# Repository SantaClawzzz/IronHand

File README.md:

# Ironhand keyboard

A full-sized keyboard in ZMK. Features a colored TFT screen, encoder, bluetooth connection and a battery.<br>
Numpad is on the left side and switches are easily replaceable with hotswap sockets. Tarkov themed.

* Keyboard specs:
  * 1 nice!nano v2 or nrf52840 pro Micro devkit
  * 1 MCP23S17-E_SO
  * 102 switches (MX)
  * 102 DO-35 diodes (1N4148)
  * 60 100nF 0603 capacitors (Any 100nF)
  * 103 LEDs (WS2812-2020) [One LED under the MCU]
  * One 2000mAh 3.7V LiPo Battery [Bridge the Charging pads under nice!nano]
  * 1 battery connector (JST PH 2.0)
  * 1 0.96" TFT SPI screen
  * 1 encoder
  * 1 button (TL3305A, optional)

## Electronics

The PCB order can be expensive, mostly shipping due to the size. I recommend ordering at least 10 (5 is minimum).<br>
The soldering is mostly fine, hotswap sockets and capacitors are easy but the LEDs are a pain.<br>
My recommendation:
* Solder one corner of the 4 pads on the entire row
* Take a LED and match the polarity
* Solder only by the corner for the entire row
* Then go backwards and solder the same side other corner, turn it and do the other side
  * Easier to do one side at a time
  * Holding the solder iron in the right hand do the right side of the LED
  * Then turn it 180 degrees and solder the other side
  * But to each their own
* the MCP soldering is basically the same, do one corner, align it, then solder the rest of the pins
* Keep in mind that the devkit has a pad under it that needs to be bridged to charge faster if you have a battery bigger than 500mAh!
* Also there is a LED under the devkit on the PCB, solder them first then the devkit on it.
* Otherwise without a desolder gun, you're gonna have a bad time.

## Mechanics

If you wish to change the project files, go ahead. It was designed in Fusion.
Printed with PETG and mostly default settings.
Two halves were attached with a metal plate and staples melted into the PETG halves.

## Firmware

* Connect USB-C
* Open ***Actions*** tab in this github repository
* Download the firmware <br>

* Double press the reset button on the keyboard and drop the file into the file system
  * If you are in bootloader the red LED will constantly blink (nrf pro Micro devkit)

## Notes to consider when building custom keyboard

Read the documentation thoroughly, the directory of the files is VERY IMPORTANT.<br>
It's much more restrict than QMK so it will take some time.<br>
Just try to get it to compile wihtout much code and then start adding features.

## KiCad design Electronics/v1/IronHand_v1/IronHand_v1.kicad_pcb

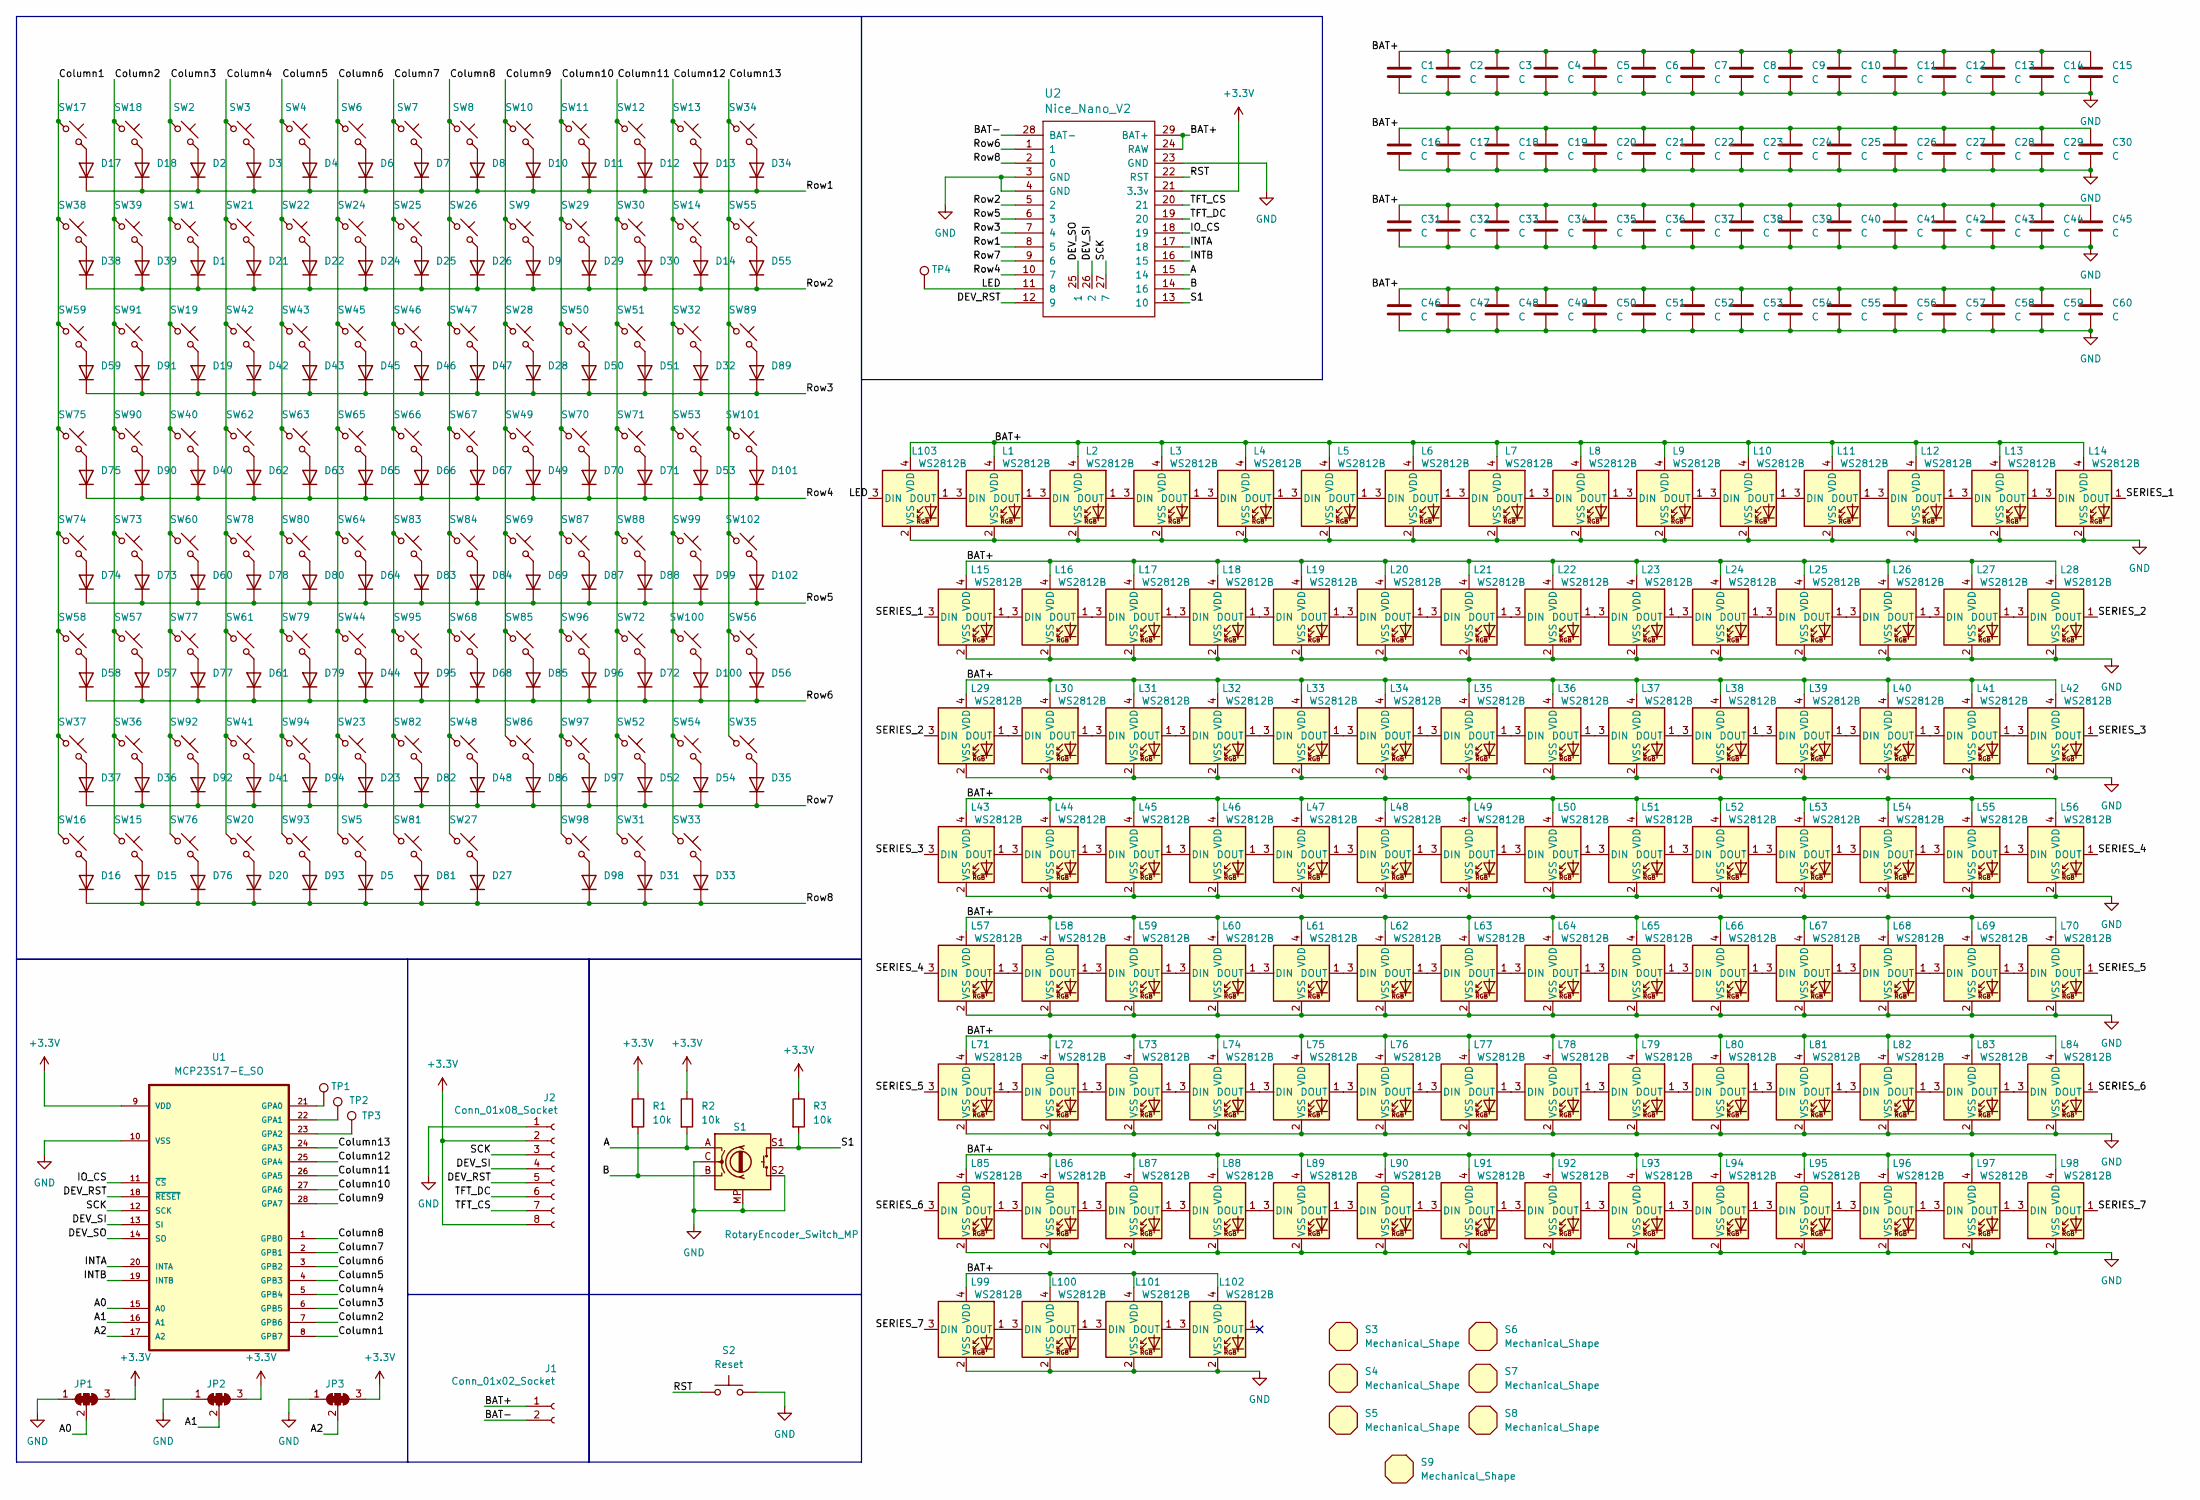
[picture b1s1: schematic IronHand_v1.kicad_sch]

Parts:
C1, C2, C3, C4, C5, C6, C7, C8, C9, C10, C11, C12, C13, C14, C15, C16, C17, C18, C19, C20, C21, C22, C23, C24, C25, C26, C27, C28, C29, C30, C31, C32, C33, C34, C35, C36, C37, C38, C39, C40, C41, C42, C43, C44, C45, C46, C47, C48, C49, C50, C51, C52, C53, C54, C55, C56, C57, C58, C59, C60: C; C_0603_1608Metric_Pad1.08x0.95mm_HandSolder
D1, D2, D3, D4, D5, D6, D7, D8, D9, D10, D11, D12, D13, D14, D15, D16, D17, D18, D19, D20, D21, D22, D23, D24, D25, D26, D27, D28, D29, D30, D31, D32, D33, D34, D35, D36, D37, D38, D39, D40, D41, D42, D43, D44, D45, D46, D47, D48, D49, D50, D51, D52, D53, D54, D55, D56, D57, D58, D59, D60, D61, D62, D63, D64, D65, D66, D67, D68, D69, D70, D71, D72, D73, D74, D75, D76, D77, D78, D79, D80, D81, D82, D83, D84, D85, D86, D87, D88, D89, D90, D91, D92, D93, D94, D95, D96, D97, D98, D99, D100, D101, D102: D; Diode_DO-35
J1: Conn_01x02_Socket; JST_PH_B2B-PH-K_1x02_P2.00mm_Vertical
J2: Conn_01x08_Socket; PinHeader_1x08_P2.54mm_Vertical
JP1, JP2, JP3: SolderJumper_3_Bridged123; SolderJumper-3_P2.0mm_Open_TrianglePad1.0x1.5mm_NumberLabels
L1, L2, L3, L4, L5, L6, L7, L8, L9, L10, L11, L12, L13, L14, L15, L16, L17, L18, L19, L20, L21, L22, L23, L24, L25, L26, L27, L28, L29, L30, L31, L32, L33, L34, L35, L36, L37, L38, L39, L40, L41, L42, L43, L44, L45, L46, L47, L48, L49, L50, L51, L52, L53, L54, L55, L56, L57, L58, L59, L60, L61, L62, L63, L64, L65, L66, L67, L68, L69, L70, L71, L72, L73, L74, L75, L76, L77, L78, L79, L80, L81, L82, L83, L84, L85, L86, L87, L88, L89, L90, L91, L92, L93, L94, L95, L96, L97, L98, L99, L100, L101, L102, L103: WS2812B; LED_WS2812B-2020_PLCC4_2.0x2.0mm
R1, R2, R3: 10k; R_0603_1608Metric_Pad0.98x0.95mm_HandSolder
S1: RotaryEncoder_Switch_MP; RotaryEncoder_Alps_EC12E-Switch_Vertical_H20mm
S2: Reset; SW_SPST_TL3305A
S3, S4, S5, S7, S8, S9: Mechanical_Shape; Stabilizer_MX_2.00u
S6: Mechanical_Shape; Stabilizer_MX_6.25u
SW1, SW2, SW3, SW4, SW5, SW6, SW7, SW8, SW9, SW10, SW11, SW12, SW13, SW14, SW15, SW16, SW17, SW18, SW19, SW20, SW21, SW22, SW23, SW24, SW25, SW26, SW27, SW28, SW29, SW30, SW31, SW33, SW34, SW35, SW36, SW37, SW38, SW41, SW42, SW43, SW44, SW45, SW46, SW47, SW48, SW49, SW50, SW51, SW52, SW54, SW55, SW56, SW57, SW58, SW59, SW60, SW61, SW62, SW63, SW64, SW65, SW66, SW67, SW68, SW69, SW70, SW71, SW72, SW73, SW74, SW75, SW78, SW79, SW80, SW81, SW82, SW83, SW84, SW85, SW86, SW87, SW89, SW91, SW99, SW100, SW101, SW102: SW_Push_45deg; Hotswap_MX_1.00u
SW32: SW_Push_45deg; Hotswap_MX_1.75u
SW39, SW90: SW_Push_45deg; Hotswap_MX_2.00u
SW40, SW92, SW93, SW94, SW96, SW97, SW98: SW_Push_45deg; Hotswap_MX_1.25u
SW53: SW_Push_45deg; Hotswap_MX_ISOEnter
SW76, SW77: SW_Push_45deg; Hotswap_MX_2.00u_90deg
SW88: SW_Push_45deg; Hotswap_MX_2.75u
SW95: SW_Push_45deg; Hotswap_MX_6.25u
TP1, TP2, TP3, TP4: TestPoint; TestPoint_Keystone_5015_Micro_Mini
U1: MCP23S17-E_SO; SOIC127P1030X265-28N
U2: Nice_Nano_V2

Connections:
+3.3V: J2.2, J2.8, JP1.3 (B), JP2.3 (B), JP3.3 (B), R1.1, R2.1, R3.1, U1.9 (VDD), U2.21 (3.3v)
/A: R2.2, S1.A, U2.15 (14)
/A0: JP1.2 (C), U1.15 (A0)
/A1: JP2.2 (C), U1.16 (A1)
/A2: JP3.2 (C), U1.17 (A2)
/B: R1.2, S1.B, U2.14 (16)
/BAT+: C1.1, C2.1, C3.1, C4.1, C5.1, C6.1, C7.1, C8.1, C9.1, C10.1, C11.1, C12.1, C13.1, C14.1, C15.1, C16.1, C17.1, C18.1, C19.1, C20.1, C21.1, C22.1, C23.1, C24.1, C25.1, C26.1, C27.1, C28.1, C29.1, C30.1, C31.1, C32.1, C33.1, C34.1, C35.1, C36.1, C37.1, C38.1, C39.1, C40.1, C41.1, C42.1, C43.1, C44.1, C45.1, C46.1, C47.1, C48.1, C49.1, C50.1, C51.1, C52.1, C53.1, C54.1, C55.1, C56.1, C57.1, C58.1, C59.1, C60.1, J1.1, L1.4 (VDD), L2.4 (VDD), L3.4 (VDD), L4.4 (VDD), L5.4 (VDD), L6.4 (VDD), L7.4 (VDD), L8.4 (VDD), L9.4 (VDD), L10.4 (VDD), L11.4 (VDD), L12.4 (VDD), L13.4 (VDD), L14.4 (VDD), L15.4 (VDD), L16.4 (VDD), L17.4 (VDD), L18.4 (VDD), L19.4 (VDD), L20.4 (VDD), L21.4 (VDD), L22.4 (VDD), L23.4 (VDD), L24.4 (VDD), L25.4 (VDD), L26.4 (VDD), L27.4 (VDD), L28.4 (VDD), L29.4 (VDD), L30.4 (VDD), L31.4 (VDD), L32.4 (VDD), L33.4 (VDD), L34.4 (VDD), L35.4 (VDD), L36.4 (VDD), L37.4 (VDD), L38.4 (VDD), L39.4 (VDD), L40.4 (VDD), L41.4 (VDD), L42.4 (VDD), L43.4 (VDD), L44.4 (VDD), L45.4 (VDD), L46.4 (VDD), L47.4 (VDD), L48.4 (VDD), L49.4 (VDD), L50.4 (VDD), L51.4 (VDD), L52.4 (VDD), L53.4 (VDD), L54.4 (VDD), L55.4 (VDD), L56.4 (VDD), L57.4 (VDD), L58.4 (VDD), L59.4 (VDD), L60.4 (VDD), L61.4 (VDD), L62.4 (VDD), L63.4 (VDD), L64.4 (VDD), L65.4 (VDD), L66.4 (VDD), L67.4 (VDD), L68.4 (VDD), L69.4 (VDD), L70.4 (VDD), L71.4 (VDD), L72.4 (VDD), L73.4 (VDD), L74.4 (VDD), L75.4 (VDD), L76.4 (VDD), L77.4 (VDD), L78.4 (VDD), L79.4 (VDD), L80.4 (VDD), L81.4 (VDD), L82.4 (VDD), L83.4 (VDD), L84.4 (VDD), L85.4 (VDD), L86.4 (VDD), L87.4 (VDD), L88.4 (VDD), L89.4 (VDD), L90.4 (VDD), L91.4 (VDD), L92.4 (VDD), L93.4 (VDD), L94.4 (VDD), L95.4 (VDD), L96.4 (VDD), L97.4 (VDD), L98.4 (VDD), L99.4 (VDD), L100.4 (VDD), L101.4 (VDD), L102.4 (VDD), L103.4 (VDD), U2.24 (RAW), U2.29 (BAT+)
/BAT-: J1.2, U2.28 (BAT-)
/Column1: SW16.1, SW17.1, SW37.1, SW38.1, SW58.1, SW59.1, SW74.1, SW75.1, U1.8 (GPB7)
/Column2: SW15.1, SW18.1, SW36.1, SW39.1, SW57.1, SW73.1, SW90.1, SW91.1, U1.7 (GPB6)
/Column3: SW1.1, SW2.1, SW19.1, SW40.1, SW60.1, SW76.1, SW77.1, SW92.1, U1.6 (GPB5)
/Column4: SW3.1, SW20.1, SW21.1, SW41.1, SW42.1, SW61.1, SW62.1, SW78.1, U1.5 (GPB4)
/Column5: SW4.1, SW22.1, SW43.1, SW63.1, SW79.1, SW80.1, SW93.1, SW94.1, U1.4 (GPB3)
/Column6: SW5.1, SW6.1, SW23.1, SW24.1, SW44.1, SW45.1, SW64.1, SW65.1, U1.3 (GPB2)
/Column7: SW7.1, SW25.1, SW46.1, SW66.1, SW81.1, SW82.1, SW83.1, SW95.1, U1.2 (GPB1)
/Column8: SW8.1, SW26.1, SW27.1, SW47.1, SW48.1, SW67.1, SW68.1, SW84.1, U1.1 (GPB0)
/Column9: SW9.1, SW10.1, SW28.1, SW49.1, SW69.1, SW85.1, SW86.1, U1.28 (GPA7)
/Column10: SW11.1, SW29.1, SW50.1, SW70.1, SW87.1, SW96.1, SW97.1, SW98.1, U1.27 (GPA6)
/Column11: SW12.1, SW30.1, SW31.1, SW51.1, SW52.1, SW71.1, SW72.1, SW88.1, U1.26 (GPA5)
/Column12: SW13.1, SW14.1, SW32.1, SW33.1, SW53.1, SW54.1, SW99.1, SW100.1, U1.25 (GPA4)
/Column13: SW34.1, SW35.1, SW55.1, SW56.1, SW89.1, SW101.1, SW102.1, U1.24 (GPA3)
/DEV_RST: J2.5, U1.18 (~RESET), U2.12 (9)
/DEV_SI: J2.4, U1.13 (SI), U2.26 (2)
/DEV_SO: U1.14 (SO), U2.25 (1)
/INTA: U1.20 (INTA), U2.17 (18)
/INTB: U1.19 (INTB), U2.16 (15)
/IO_CS: U1.11 (~CS), U2.18 (19)
/LED: L103.3 (DIN), TP4.1 (1_1), U2.11 (8)
/RST: S2.1, U2.22 (RST)
/Row1: D2.1 (K), D3.1 (K), D4.1 (K), D6.1 (K), D7.1 (K), D8.1 (K), D10.1 (K), D11.1 (K), D12.1 (K), D13.1 (K), D17.1 (K), D18.1 (K), D34.1 (K), U2.8 (5)
/Row2: D1.1 (K), D9.1 (K), D14.1 (K), D21.1 (K), D22.1 (K), D24.1 (K), D25.1 (K), D26.1 (K), D29.1 (K), D30.1 (K), D38.1 (K), D39.1 (K), D55.1 (K), U2.5 (2)
/Row3: D19.1 (K), D28.1 (K), D32.1 (K), D42.1 (K), D43.1 (K), D45.1 (K), D46.1 (K), D47.1 (K), D50.1 (K), D51.1 (K), D59.1 (K), D89.1 (K), D91.1 (K), U2.7 (4)
/Row4: D40.1 (K), D49.1 (K), D53.1 (K), D62.1 (K), D63.1 (K), D65.1 (K), D66.1 (K), D67.1 (K), D70.1 (K), D71.1 (K), D75.1 (K), D90.1 (K), D101.1 (K), U2.10 (7)
/Row5: D60.1 (K), D64.1 (K), D69.1 (K), D73.1 (K), D74.1 (K), D78.1 (K), D80.1 (K), D83.1 (K), D84.1 (K), D87.1 (K), D88.1 (K), D99.1 (K), D102.1 (K), U2.6 (3)
/Row6: D44.1 (K), D56.1 (K), D57.1 (K), D58.1 (K), D61.1 (K), D68.1 (K), D72.1 (K), D77.1 (K), D79.1 (K), D85.1 (K), D95.1 (K), D96.1 (K), D100.1 (K), U2.1
/Row7: D23.1 (K), D35.1 (K), D36.1 (K), D37.1 (K), D41.1 (K), D48.1 (K), D52.1 (K), D54.1 (K), D82.1 (K), D86.1 (K), D92.1 (K), D94.1 (K), D97.1 (K), U2.9 (6)
/Row8: D5.1 (K), D15.1 (K), D16.1 (K), D20.1 (K), D27.1 (K), D31.1 (K), D33.1 (K), D76.1 (K), D81.1 (K), D93.1 (K), D98.1 (K), U2.2 (0)
/S1: R3.2, S1.S1, U2.13 (10)
/SCK: J2.3, U1.12 (SCK), U2.27 (7)
/SERIES_1: L14.1 (DOUT), L15.3 (DIN)
/SERIES_2: L28.1 (DOUT), L29.3 (DIN)
/SERIES_3: L42.1 (DOUT), L43.3 (DIN)
/SERIES_4: L56.1 (DOUT), L57.3 (DIN)
/SERIES_5: L70.1 (DOUT), L71.3 (DIN)
/SERIES_6: L84.1 (DOUT), L85.3 (DIN)
/SERIES_7: L98.1 (DOUT), L99.3 (DIN)
/TFT_CS: J2.7, U2.20 (21)
/TFT_DC: J2.6, U2.19 (20)
GND: C1.2, C2.2, C3.2, C4.2, C5.2, C6.2, C7.2, C8.2, C9.2, C10.2, C11.2, C12.2, C13.2, C14.2, C15.2, C16.2, C17.2, C18.2, C19.2, C20.2, C21.2, C22.2, C23.2, C24.2, C25.2, C26.2, C27.2, C28.2, C29.2, C30.2, C31.2, C32.2, C33.2, C34.2, C35.2, C36.2, C37.2, C38.2, C39.2, C40.2, C41.2, C42.2, C43.2, C44.2, C45.2, C46.2, C47.2, C48.2, C49.2, C50.2, C51.2, C52.2, C53.2, C54.2, C55.2, C56.2, C57.2, C58.2, C59.2, C60.2, J2.1, JP1.1 (A), JP2.1 (A), JP3.1 (A), L1.2 (VSS), L2.2 (VSS), L3.2 (VSS), L4.2 (VSS), L5.2 (VSS), L6.2 (VSS), L7.2 (VSS), L8.2 (VSS), L9.2 (VSS), L10.2 (VSS), L11.2 (VSS), L12.2 (VSS), L13.2 (VSS), L14.2 (VSS), L15.2 (VSS), L16.2 (VSS), L17.2 (VSS), L18.2 (VSS), L19.2 (VSS), L20.2 (VSS), L21.2 (VSS), L22.2 (VSS), L23.2 (VSS), L24.2 (VSS), L25.2 (VSS), L26.2 (VSS), L27.2 (VSS), L28.2 (VSS), L29.2 (VSS), L30.2 (VSS), L31.2 (VSS), L32.2 (VSS), L33.2 (VSS), L34.2 (VSS), L35.2 (VSS), L36.2 (VSS), L37.2 (VSS), L38.2 (VSS), L39.2 (VSS), L40.2 (VSS), L41.2 (VSS), L42.2 (VSS), L43.2 (VSS), L44.2 (VSS), L45.2 (VSS), L46.2 (VSS), L47.2 (VSS), L48.2 (VSS), L49.2 (VSS), L50.2 (VSS), L51.2 (VSS), L52.2 (VSS), L53.2 (VSS), L54.2 (VSS), L55.2 (VSS), L56.2 (VSS), L57.2 (VSS), L58.2 (VSS), L59.2 (VSS), L60.2 (VSS), L61.2 (VSS), L62.2 (VSS), L63.2 (VSS), L64.2 (VSS), L65.2 (VSS), L66.2 (VSS), L67.2 (VSS), L68.2 (VSS), L69.2 (VSS), L70.2 (VSS), L71.2 (VSS), L72.2 (VSS), L73.2 (VSS), L74.2 (VSS), L75.2 (VSS), L76.2 (VSS), L77.2 (VSS), L78.2 (VSS), L79.2 (VSS), L80.2 (VSS), L81.2 (VSS), L82.2 (VSS), L83.2 (VSS), L84.2 (VSS), L85.2 (VSS), L86.2 (VSS), L87.2 (VSS), L88.2 (VSS), L89.2 (VSS), L90.2 (VSS), L91.2 (VSS), L92.2 (VSS), L93.2 (VSS), L94.2 (VSS), L95.2 (VSS), L96.2 (VSS), L97.2 (VSS), L98.2 (VSS), L99.2 (VSS), L100.2 (VSS), L101.2 (VSS), L102.2 (VSS), L103.2 (VSS), S1.C, S1.MP, S1.S2, S2.2, U1.10 (VSS), U2.3 (GND), U2.4 (GND), U2.23 (GND)
unnamed: D1.2 (A), SW1.2
unnamed: D2.2 (A), SW2.2
unnamed: D3.2 (A), SW3.2
unnamed: D4.2 (A), SW4.2
unnamed: D5.2 (A), SW5.2
unnamed: D6.2 (A), SW6.2
unnamed: D7.2 (A), SW7.2
unnamed: D8.2 (A), SW8.2
unnamed: D9.2 (A), SW9.2
unnamed: D10.2 (A), SW10.2
unnamed: D11.2 (A), SW11.2
unnamed: D12.2 (A), SW12.2
unnamed: D13.2 (A), SW13.2
unnamed: D14.2 (A), SW14.2
unnamed: D15.2 (A), SW15.2
unnamed: D16.2 (A), SW16.2
unnamed: D17.2 (A), SW17.2
unnamed: D18.2 (A), SW18.2
unnamed: D19.2 (A), SW19.2
unnamed: D20.2 (A), SW20.2
unnamed: D21.2 (A), SW21.2
unnamed: D22.2 (A), SW22.2
unnamed: D23.2 (A), SW23.2
unnamed: D24.2 (A), SW24.2
unnamed: D25.2 (A), SW25.2
unnamed: D26.2 (A), SW26.2
unnamed: D27.2 (A), SW27.2
unnamed: D28.2 (A), SW28.2
unnamed: D29.2 (A), SW29.2
unnamed: D30.2 (A), SW30.2
unnamed: D31.2 (A), SW31.2
unnamed: D32.2 (A), SW32.2
unnamed: D33.2 (A), SW33.2
unnamed: D34.2 (A), SW34.2
unnamed: D35.2 (A), SW35.2
unnamed: D36.2 (A), SW36.2
unnamed: D37.2 (A), SW37.2
unnamed: D38.2 (A), SW38.2
unnamed: D39.2 (A), SW39.2
unnamed: D40.2 (A), SW40.2
unnamed: D41.2 (A), SW41.2
unnamed: D42.2 (A), SW42.2
unnamed: D43.2 (A), SW43.2
unnamed: D44.2 (A), SW44.2
unnamed: D45.2 (A), SW45.2
unnamed: D46.2 (A), SW46.2
unnamed: D47.2 (A), SW47.2
unnamed: D48.2 (A), SW48.2
unnamed: D49.2 (A), SW49.2
unnamed: D50.2 (A), SW50.2
unnamed: D51.2 (A), SW51.2
unnamed: D52.2 (A), SW52.2
unnamed: D53.2 (A), SW53.2
unnamed: D54.2 (A), SW54.2
unnamed: D55.2 (A), SW55.2
unnamed: D56.2 (A), SW56.2
unnamed: D57.2 (A), SW57.2
unnamed: D58.2 (A), SW58.2
unnamed: D59.2 (A), SW59.2
unnamed: D60.2 (A), SW60.2
unnamed: D61.2 (A), SW61.2
unnamed: D62.2 (A), SW62.2
unnamed: D63.2 (A), SW63.2
unnamed: D64.2 (A), SW64.2
unnamed: D65.2 (A), SW65.2
unnamed: D66.2 (A), SW66.2
unnamed: D67.2 (A), SW67.2
unnamed: D68.2 (A), SW68.2
unnamed: D69.2 (A), SW69.2
unnamed: D70.2 (A), SW70.2
unnamed: D71.2 (A), SW71.2
unnamed: D72.2 (A), SW72.2
unnamed: D73.2 (A), SW73.2
unnamed: D74.2 (A), SW74.2
unnamed: D75.2 (A), SW75.2
unnamed: D76.2 (A), SW76.2
unnamed: D77.2 (A), SW77.2
unnamed: D78.2 (A), SW78.2
unnamed: D79.2 (A), SW79.2
unnamed: D80.2 (A), SW80.2
unnamed: D81.2 (A), SW81.2
unnamed: D82.2 (A), SW82.2
unnamed: D83.2 (A), SW83.2
unnamed: D84.2 (A), SW84.2
unnamed: D85.2 (A), SW85.2
unnamed: D86.2 (A), SW86.2
unnamed: D87.2 (A), SW87.2
unnamed: D88.2 (A), SW88.2
unnamed: D89.2 (A), SW89.2
unnamed: D90.2 (A), SW90.2
unnamed: D91.2 (A), SW91.2
unnamed: D92.2 (A), SW92.2
unnamed: D93.2 (A), SW93.2
unnamed: D94.2 (A), SW94.2
unnamed: D95.2 (A), SW95.2
unnamed: D96.2 (A), SW96.2
unnamed: D97.2 (A), SW97.2
unnamed: D98.2 (A), SW98.2
unnamed: D99.2 (A), SW99.2
unnamed: D100.2 (A), SW100.2
unnamed: D101.2 (A), SW101.2
unnamed: D102.2 (A), SW102.2
unnamed: L1.3 (DIN), L103.1 (DOUT)
unnamed: L1.1 (DOUT), L2.3 (DIN)
unnamed: L2.1 (DOUT), L3.3 (DIN)
unnamed: L3.1 (DOUT), L4.3 (DIN)
unnamed: L4.1 (DOUT), L5.3 (DIN)
unnamed: L5.1 (DOUT), L6.3 (DIN)
unnamed: L6.1 (DOUT), L7.3 (DIN)
unnamed: L7.1 (DOUT), L8.3 (DIN)
unnamed: L8.1 (DOUT), L9.3 (DIN)
unnamed: L9.1 (DOUT), L10.3 (DIN)
unnamed: L10.1 (DOUT), L11.3 (DIN)
unnamed: L11.1 (DOUT), L12.3 (DIN)
unnamed: L12.1 (DOUT), L13.3 (DIN)
unnamed: L13.1 (DOUT), L14.3 (DIN)
unnamed: L15.1 (DOUT), L16.3 (DIN)
unnamed: L16.1 (DOUT), L17.3 (DIN)
unnamed: L17.1 (DOUT), L18.3 (DIN)
unnamed: L18.1 (DOUT), L19.3 (DIN)
unnamed: L19.1 (DOUT), L20.3 (DIN)
unnamed: L20.1 (DOUT), L21.3 (DIN)
unnamed: L21.1 (DOUT), L22.3 (DIN)
unnamed: L22.1 (DOUT), L23.3 (DIN)
unnamed: L23.1 (DOUT), L24.3 (DIN)
unnamed: L24.1 (DOUT), L25.3 (DIN)
unnamed: L25.1 (DOUT), L26.3 (DIN)
unnamed: L26.1 (DOUT), L27.3 (DIN)
unnamed: L27.1 (DOUT), L28.3 (DIN)
unnamed: L29.1 (DOUT), L30.3 (DIN)
unnamed: L30.1 (DOUT), L31.3 (DIN)
unnamed: L31.1 (DOUT), L32.3 (DIN)
unnamed: L32.1 (DOUT), L33.3 (DIN)
unnamed: L33.1 (DOUT), L34.3 (DIN)
unnamed: L34.1 (DOUT), L35.3 (DIN)
unnamed: L35.1 (DOUT), L36.3 (DIN)
unnamed: L36.1 (DOUT), L37.3 (DIN)
unnamed: L37.1 (DOUT), L38.3 (DIN)
unnamed: L38.1 (DOUT), L39.3 (DIN)
unnamed: L39.1 (DOUT), L40.3 (DIN)
unnamed: L40.1 (DOUT), L41.3 (DIN)
unnamed: L41.1 (DOUT), L42.3 (DIN)
unnamed: L43.1 (DOUT), L44.3 (DIN)
unnamed: L44.1 (DOUT), L45.3 (DIN)
unnamed: L45.1 (DOUT), L46.3 (DIN)
unnamed: L46.1 (DOUT), L47.3 (DIN)
unnamed: L47.1 (DOUT), L48.3 (DIN)
unnamed: L48.1 (DOUT), L49.3 (DIN)
unnamed: L49.1 (DOUT), L50.3 (DIN)
unnamed: L50.1 (DOUT), L51.3 (DIN)
unnamed: L51.1 (DOUT), L52.3 (DIN)
unnamed: L52.1 (DOUT), L53.3 (DIN)
unnamed: L53.1 (DOUT), L54.3 (DIN)
unnamed: L54.1 (DOUT), L55.3 (DIN)
unnamed: L55.1 (DOUT), L56.3 (DIN)
unnamed: L57.1 (DOUT), L58.3 (DIN)
unnamed: L58.1 (DOUT), L59.3 (DIN)
unnamed: L59.1 (DOUT), L60.3 (DIN)
unnamed: L60.1 (DOUT), L61.3 (DIN)
unnamed: L61.1 (DOUT), L62.3 (DIN)
unnamed: L62.1 (DOUT), L63.3 (DIN)
unnamed: L63.1 (DOUT), L64.3 (DIN)
unnamed: L64.1 (DOUT), L65.3 (DIN)
unnamed: L65.1 (DOUT), L66.3 (DIN)
unnamed: L66.1 (DOUT), L67.3 (DIN)
unnamed: L67.1 (DOUT), L68.3 (DIN)
unnamed: L68.1 (DOUT), L69.3 (DIN)
unnamed: L69.1 (DOUT), L70.3 (DIN)
unnamed: L71.1 (DOUT), L72.3 (DIN)
unnamed: L72.1 (DOUT), L73.3 (DIN)
unnamed: L73.1 (DOUT), L74.3 (DIN)
unnamed: L74.1 (DOUT), L75.3 (DIN)
unnamed: L75.1 (DOUT), L76.3 (DIN)
unnamed: L76.1 (DOUT), L77.3 (DIN)
unnamed: L77.1 (DOUT), L78.3 (DIN)
unnamed: L78.1 (DOUT), L79.3 (DIN)
unnamed: L79.1 (DOUT), L80.3 (DIN)
unnamed: L80.1 (DOUT), L81.3 (DIN)
unnamed: L81.1 (DOUT), L82.3 (DIN)
unnamed: L82.1 (DOUT), L83.3 (DIN)
unnamed: L83.1 (DOUT), L84.3 (DIN)
unnamed: L85.1 (DOUT), L86.3 (DIN)
unnamed: L86.1 (DOUT), L87.3 (DIN)
unnamed: L87.1 (DOUT), L88.3 (DIN)
unnamed: L88.1 (DOUT), L89.3 (DIN)
unnamed: L89.1 (DOUT), L90.3 (DIN)
unnamed: L90.1 (DOUT), L91.3 (DIN)
unnamed: L91.1 (DOUT), L92.3 (DIN)
unnamed: L92.1 (DOUT), L93.3 (DIN)
unnamed: L93.1 (DOUT), L94.3 (DIN)
unnamed: L94.1 (DOUT), L95.3 (DIN)
unnamed: L95.1 (DOUT), L96.3 (DIN)
unnamed: L96.1 (DOUT), L97.3 (DIN)
unnamed: L97.1 (DOUT), L98.3 (DIN)
unnamed: L99.1 (DOUT), L100.3 (DIN)
unnamed: L100.1 (DOUT), L101.3 (DIN)
unnamed: L101.1 (DOUT), L102.3 (DIN)
unnamed: TP1.1 (1_1), U1.21 (GPA0)
unnamed: TP2.1 (1_1), U1.22 (GPA1)
unnamed: TP3.1 (1_1), U1.23 (GPA2)

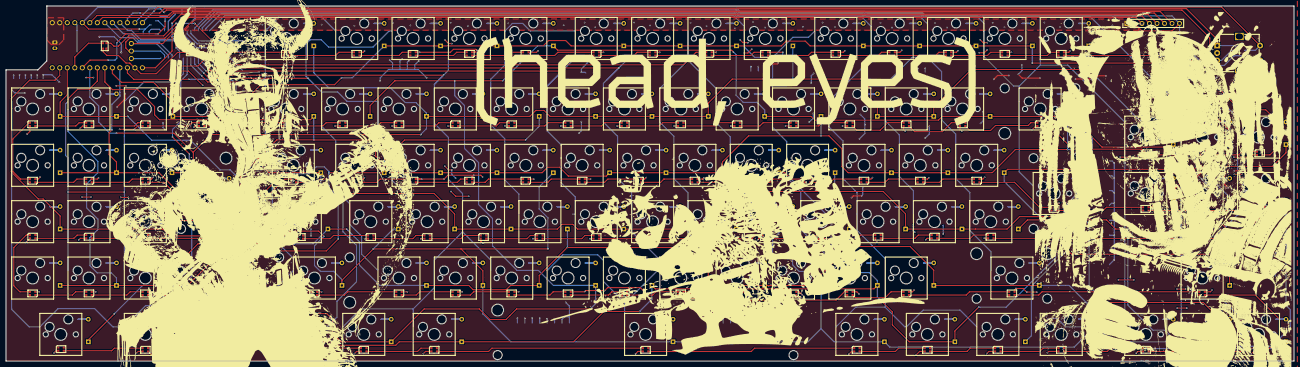
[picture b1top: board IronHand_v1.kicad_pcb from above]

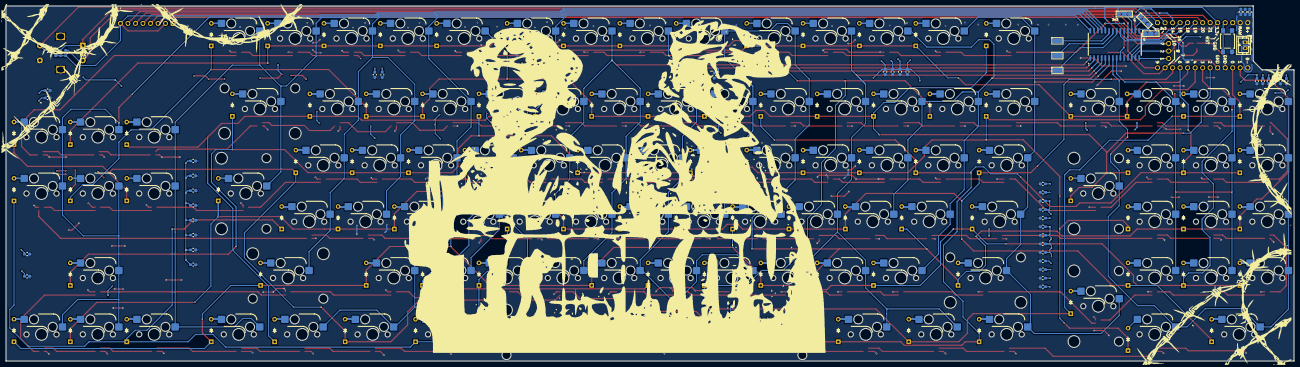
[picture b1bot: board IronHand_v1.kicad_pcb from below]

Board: 2 copper layers, 435.3 x 120.0 mm, 390 parts (174 on the bottom side), 249 nets.

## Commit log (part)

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2025-11-11 Initial User Config.
2025-11-11 Yaml change
2025-11-11 Initial commit after ZMK guidelines fixes
2025-11-11 Added boards directory to conf as well
2025-11-11 Kconfig in config and boards in boards
2025-11-11 Added boards as well
2025-11-11 Removed shield option, opting to use just as board in config folder
2025-11-11 Added more boards@
2025-11-11 Re do
2025-11-12 Fixin yaml
2025-11-12 Maybe fixed
2025-11-12 Adding boards folders
2025-11-12 boards folder add
2025-11-12 Added Evert.conf
2025-11-12 Fixed file names
2025-11-12 move to config folder
2025-11-12 Renamed to evert.
2025-11-12 Added Evert folder
2025-11-12 Pin enables
2025-11-12 Rename of conf and defconf
2025-11-12 Renamed to ksca0 in hopes of GPIOs already defined
2025-11-12 Wrong labels
2025-11-12 Changes from nice60 board 1/2
2025-11-12 One change missed
2025-11-12 Second change missed
2025-11-12 Third change missed
2025-11-12 Fourth change missed
2025-11-12 Nice60 chanes 2/2
2025-11-13 Added partion node to chosen
2025-11-13 Added ext power and vbatt nodes
2025-11-13 ksca0 to kscan0
2025-11-13 Removed the added confs from one head ago
2025-11-13 Ksca0 to kscna0 again
2025-11-13 Added configs
2025-11-13 Changed the board nice60 conf
2025-11-13 Removed the LED configs for now
2025-11-20 Added Kconfig files from nice!60
2025-11-20 All nice!60 files copied
2025-11-20 Remove code_partition
2025-11-20 Changed board from nicenanov2 to nicenano
2025-12-18 Change of directory
2026-03-26 WS2812 test
2026-03-26 Roll back
2026-03-27 New WS test
2026-03-27 ReadMe and name change
2026-03-28 Tagilla silk
2026-03-28 Forgot to save
2026-04-03 v1 production
2026-04-20 v1 first test
2026-04-20 MCP driver push
2026-04-20 MCP ngpio fix
2026-04-20 dts/binding delete due to duplication
2026-04-20 int and reset gpio delete
2026-04-20 gpio fix, last flashed
2026-04-20 nice_nano_v2 fix
2026-04-20 keymap keycodes fix
2026-04-20 some keycodes fixed
2026-04-20 numpad fix back
2026-04-20 test insert
2026-04-20 madctl fix
2026-04-20 inv, col, pwm
2026-05-20 WS2812 chain length increase
2026-05-20 Battery fix, ADC add in config
2026-05-20 ADC implemented and RGB_TOGGLE with encoder sel
2026-05-20 removed ADC, since battery.c not used, battery is code free
2026-05-22 Display
2026-05-22 Display v2
2026-05-22 Display v3
2026-05-22 Display and LEDs
2026-05-22 Display corrpution
2026-05-22 Display byte order
2026-05-22 Hierarchy change
2026-05-22 Display fix
2026-05-22 Display fix v2
2026-05-22 Display fix v3
2026-05-25 Screen Fix Post-sub
2026-05-25 tarkov_draw_event delete
2026-05-25 CONFIG_LV_IMG_USE
2026-05-25 Roll back to Display fix v3
2026-05-25 Display fix with CoPilot
2026-05-25 0 offsets
2026-05-25 9F and 4F caset, raset
2026-05-25 20 offset
2026-05-25 0 offset, 0 madctl and def caset raset
2026-05-25 New values with image
2026-05-25 madctl 0x60
2026-05-25 y-offset 23
2026-05-25 y-offset 24
2026-05-25 status overlay
2026-05-26 Icons fix
2026-05-26 Icons fix and tarkov image
2026-05-26 Screen final v1
2026-06-08 library added to project
